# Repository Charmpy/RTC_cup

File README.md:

# RTC_cup
┈┈┈┈┈┈┈┈┈┈┈┈┈┈┈┈┈┈┈┈

┈┈┈┈┈┏┻━━┻┓┈┈┈┈┈

╭┓┏╮┈┃▕▏ ▕▏┃┈╭┓┏╮

┃┗┛┃┈┃  ┏┳┳┓  ┃┈┃┗┛┃

╰┳┳╯┈┃  ┗┻┻┛  ┃┈╰┳┳╯

┈┃┃┏━┻━━━━┻━┓┃┃┈

┈┃╰┫ ╭━━━━━━╮   ┣╯┃┈

┈╰━┫ ┃╱╲╱╲╱╲┃   ┣━╯┈

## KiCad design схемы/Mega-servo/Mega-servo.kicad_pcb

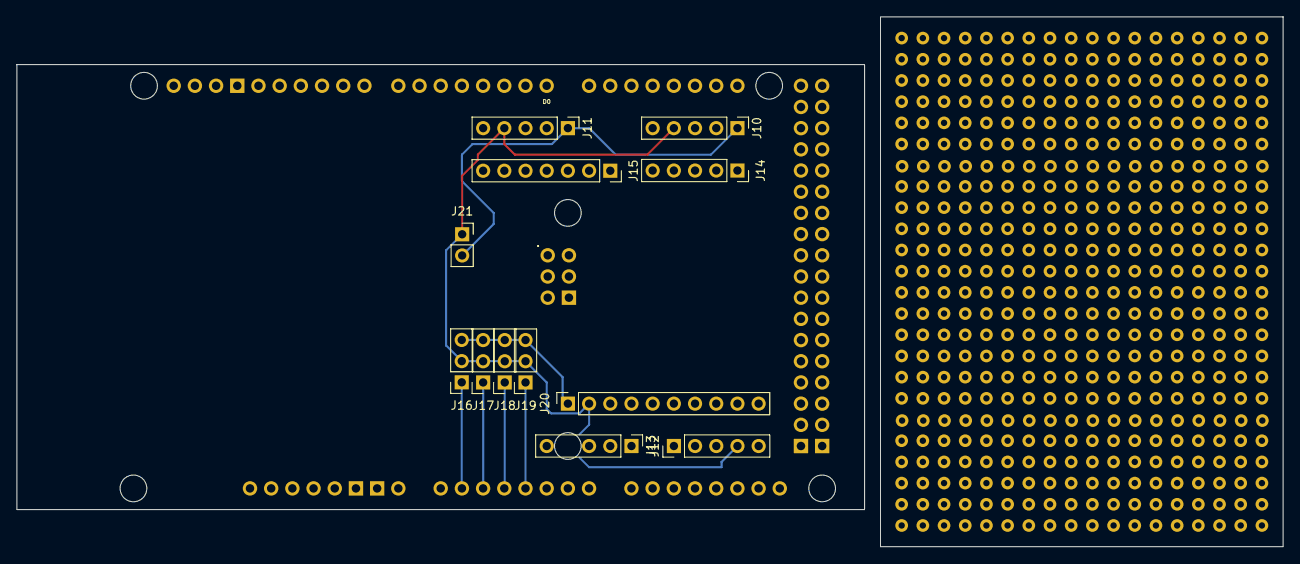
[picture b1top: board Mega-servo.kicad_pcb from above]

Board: 2 copper layers, 151.8 x 63.5 mm, 13 parts (0 on the bottom side), 17 nets.

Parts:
J10, J11, J12, J13: Conn_01x05_Pin; PinHeader_1x05_P2.54mm_Vertical
J14: Conn_01x05_Pin; PinSocket_1x05_P2.54mm_Vertical
J15: Conn_01x07; PinSocket_1x07_P2.54mm_Vertical
J16, J17, J18, J19: Conn_01x03; PinSocket_1x03_P2.54mm_Vertical
J20: Conn_01x10; PinSocket_1x10_P2.54mm_Vertical
J21: Conn_01x02; PinSocket_1x02_P2.54mm_Vertical
XA3: Arduino_Mega2560_Shield

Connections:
+5V: J16.3, J17.3, J18.3, J19.3, J20.1, XA3.5V4 (5V)
+12V: J10.1, J11.1, J12.1, J13.1, J21.2
/if_Beside/CS_74HC595: J15.3, XA3.D48
/if_Beside/MISO: J20.7, XA3.D50 (D50_MISO)
/if_Beside/MOSI: J15.7, J20.4, XA3.D51 (D51_MOSI)
/if_Beside/MR_74HC595: J14.5, XA3.D47
/if_Beside/PWM_M0: J15.6, XA3.D30
/if_Beside/PWM_M1: J15.5, XA3.D32
/if_Beside/PWM_M2: J15.4, XA3.D34
/if_Beside/PWM_M3: J14.1, XA3.D36
/if_Beside/PWM_SERVO_MAN0: J16.1, XA3.A1
/if_Beside/PWM_SERVO_MAN1: J17.1, XA3.A2
/if_Beside/PWM_SERVO_MAN2: J18.1, XA3.A3
/if_Beside/PWM_SERVO_MAN3: J19.1, XA3.A4
/if_Beside/SCK: J14.2, J20.3, XA3.D52 (D52_SCK)
/if_Beside/UartServoMX28-T: J10.5, J11.5, J12.5, J13.5, XA3.D18 (D18/TX1), XA3.D19 (D19/RX1)
GND: J10.4, J11.4, J12.4, J13.4, J15.1, J16.2, J17.2, J18.2, J19.2, J20.2, J21.1, XA3.GND1 (GND)

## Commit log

2023-03-14 Create
2023-04-20 add web
2023-04-21 asfd
2023-04-23 fyfueufgr
2023-04-29 trtrtr
2023-04-29 lalala
2023-04-29 merge
2023-04-29 Revert "lalala"
2023-05-02 joystick
2023-05-02 first raspberry
2023-05-02 first frontend
2023-05-02 first raspberrr
2023-05-02 trtrtrtr
2023-05-05 докинул схемы
2023-05-08 First TCP
2023-05-24 Joy Movement
2023-05-24 UI new
2023-05-24 Joy fix
2023-05-24 Joy fix #2
2023-05-24 Joy fix #3
2025-12-08 Создано в Colab
